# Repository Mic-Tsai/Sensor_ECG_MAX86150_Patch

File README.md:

# Sensor_ECG_PPG_MAX86150 | Patch

Arduino based sensor learning project. This project is further application from Health_Sensor_ecg_ppg_max86150 dev-board, plotting the ECG curve which used Processing on your computer.

 - Bias Cancellation | Store raw data in time, when new data coming that bias level will calculate as hysteresis filter.

 - Heart Rate Detect | Check windows will output the BPM results (ECG).

This board also support WiFi transmission via ESPNOW (ESP8266 Broadcast), and need power by battery. You need 2x esp8266 board.

1) Read receiver esp8266's mac address.
2) Fill it into the transmitter sketch. "ECG_ESP8266_MAX86150_V6"

** **A Known Issue** **

Sampling rate from MAX86150 set as 200sps, but ESP8266's multiplex with ESP-NOW and sensor hub reading task will low down the output sample rate to ~150sps. When you measuring your ECG in real-time plot may show the missing R-R interval. (R-peak missing!) Don't worry, it just the lower sample  caused.

```
Arduino tool kit, and require the following material:
- MCU: ESP8266 
- Sensor: MAX86150
```
##

For coding example, you need the following library:

* [protocentral_max86150_ecg_ppg](https://github.com/Protocentral/protocentral_max86150_ecg_ppg)

## 

Any question or need technical support:

* Contact me via mail (xbcke12345@gmail.com)

## 

## 

>### License Information
>>This product is open source! Both, our hardware and software are open source and licensed under the following:
>>#### Hardware
>>>All hardware is released under [Creative Commons Share-alike 4.0 International](http://creativecommons.org/licenses/by-sa/4.0/)
>>#### Software 
>>>All software is released under the MIT License [http://opensource.org/licenses/MIT](http://opensource.org/licenses/MIT)
>>#### Documentation
>>>The documentation on this page is released under [Creative Commons Share-alike 4.0 International](http://creativecommons.org/licenses/by-sa/4.0/)

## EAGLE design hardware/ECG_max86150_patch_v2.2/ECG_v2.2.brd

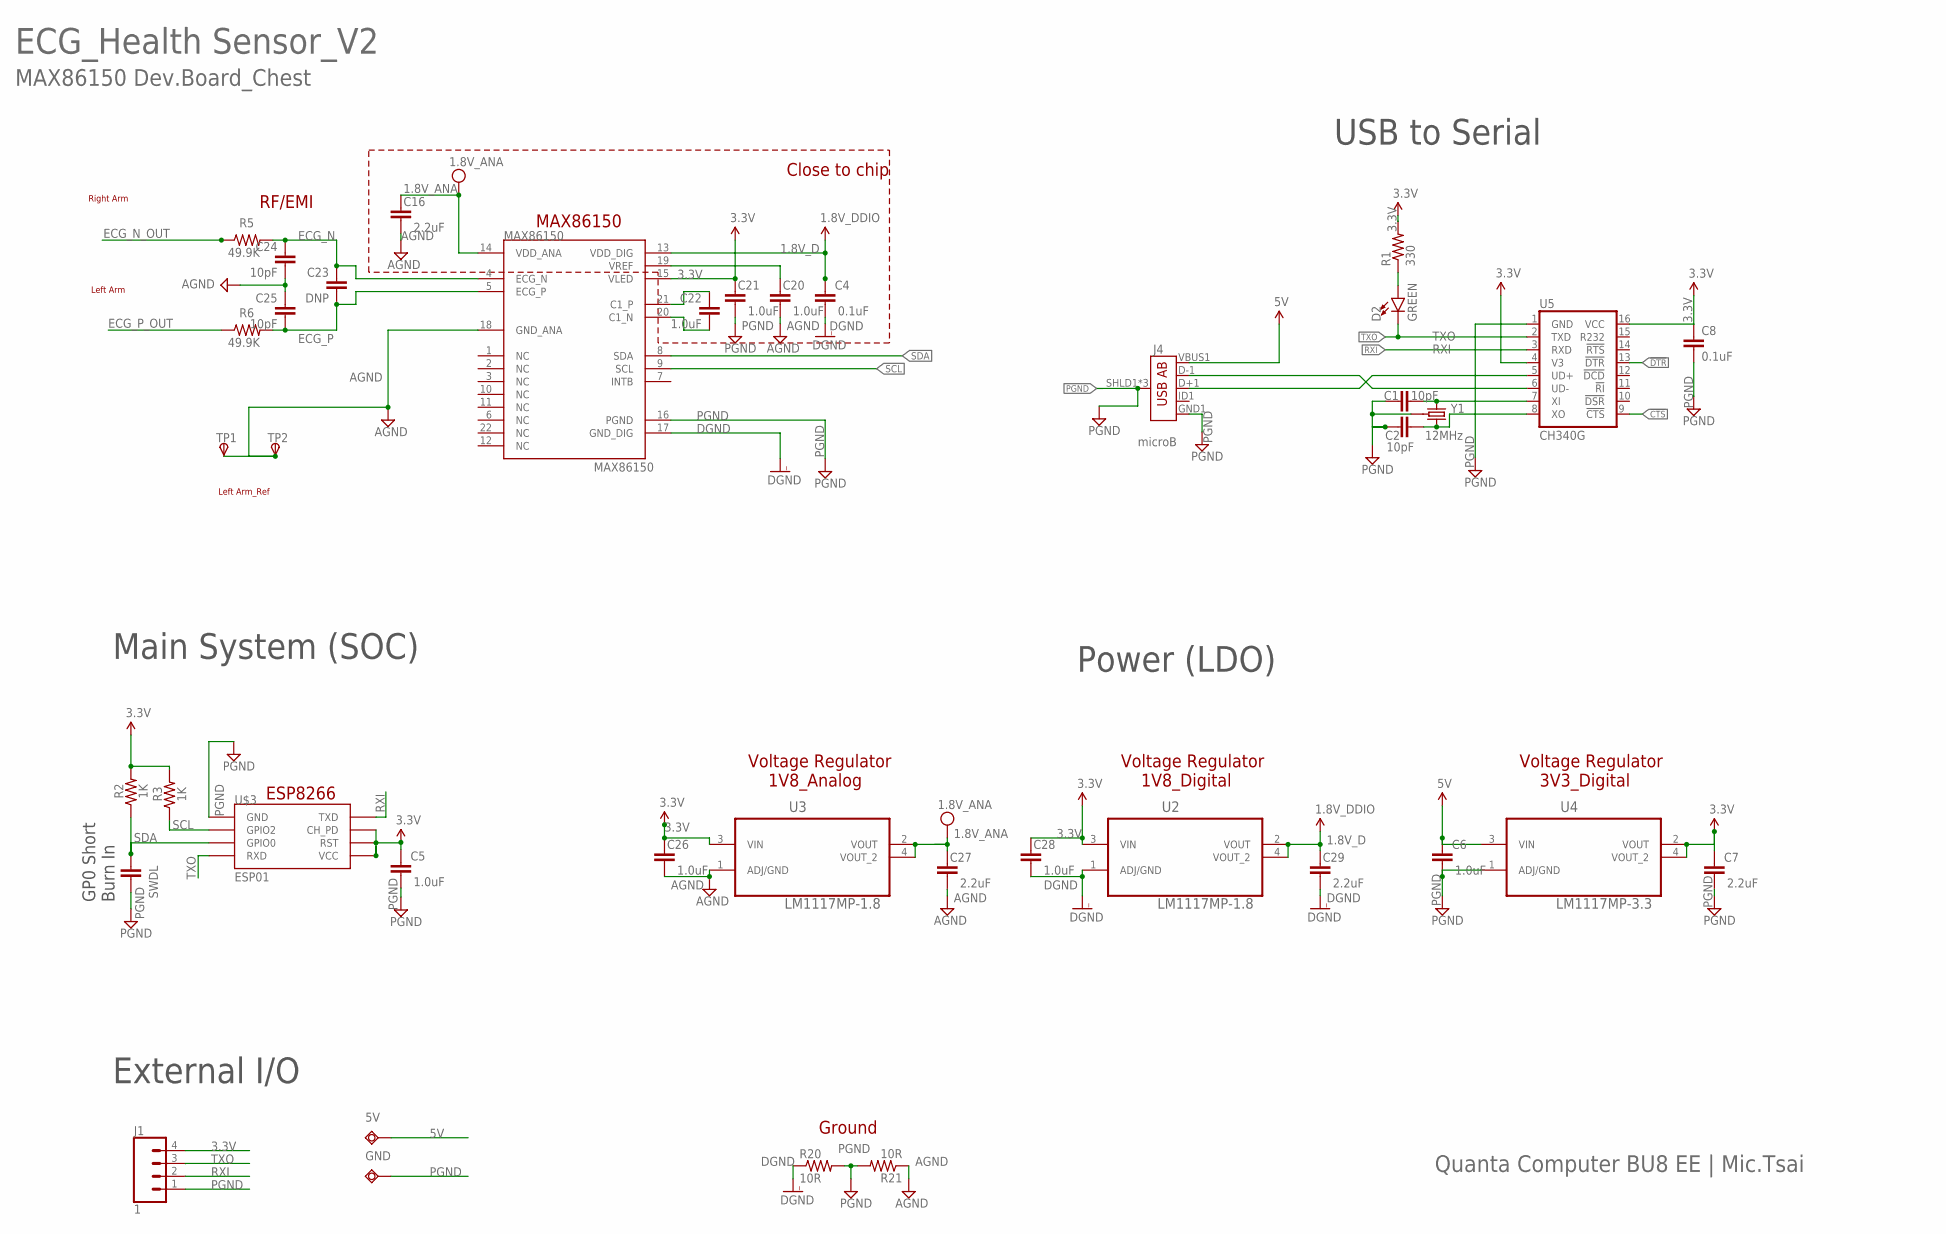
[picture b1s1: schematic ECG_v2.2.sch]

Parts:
5V: TPSQTP20R; TP20R
C1, C2: 10pF; 0603-CAP
C4: 0.1uF; 0805
C5, C6, C20, C21, C22, C26, C28: 1.0uF; 0805
C7, C16, C27, C29: 2.2uF; 0805
C8: 0.1uF; 0603-CAP
C23: DNP; 0402
C24, C25: 10pF; 0402
D2: GREEN; LED-0603
GND: TPSQTP20R; TP20R
J1: 1; 1X04
J4: microB; USB-AB-MICRO-SMD
MAX86150: MAX86150
R1: 330; 0603-RES
R2, R3: 1K; 0805
R5, R6: 49.9K; 0805
R20, R21: 10R; 0805
SWDL: 10pF; 0402
TP1, TP2: TPSB1,27; B1,27
U2, U3: LM1117MP-1.8; SOT230P696X180-4N
U4: LM1117MP-3.3; SOT230P696X180-4N
U5: CH340G; SO016
U$3: ESP01
Y1: 12MHz; CRYSTAL-SMD-3.2X2.5

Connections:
1.8V_ANA: C16.1, C27.1, MAX86150.14 (VDD_ANA), U3.2 (VOUT), U3.4 (VOUT_2)
1.8V_D: C4.1, C29.1, MAX86150.13 (VDD_DIG), U2.2 (VOUT), U2.4 (VOUT_2)
3.3V: C5.1, C7.1, C8.1, C21.1, C26.1, C28.1, J1.4, MAX86150.15 (VLED), R1.2, R2.2, R3.2, U2.3 (VIN), U3.3 (VIN), U4.2 (VOUT), U4.4 (VOUT_2), U5.4 (V3), U5.16 (VCC), U$3.CH_PD, U$3.RST, U$3.VCC
5V: 5V.TP, C6.1, J4.VBUS1 (VBUS), U4.3 (VIN)
!CTS: U5.9 (!CTS)
!DTR: U5.13 (!DTR)
AGND: C16.2, C20.2, C24.2, C25.1, C26.2, C27.2, MAX86150.18 (GND_ANA), R21.1, TP1.PP, TP2.PP, U3.1 (ADJ/GND)
DGND: C4.2, C28.2, C29.2, MAX86150.17 (GND_DIG), R20.1, U2.1 (ADJ/GND)
ECG_N: C23.1, C24.1, MAX86150.4 (ECG_N), R5.2
ECG_N_OUT: R5.1
ECG_P: C23.2, C25.2, MAX86150.5 (ECG_P), R6.2
ECG_P_OUT: R6.1
unnamed: D2.A, R1.1
unnamed: C22.1, MAX86150.21 (C1_P)
unnamed: C22.2, MAX86150.20 (C1_N)
unnamed: C20.1, MAX86150.19 (VREF)
unnamed: C2.2, U5.8 (XO), Y1.3 (2)
unnamed: C1.2, U5.7 (XI), Y1.1
unnamed: J4.D-1 (D-), U5.6 (UD-)
unnamed: J4.D+1 (D+), U5.5 (UD+)
PGND: C1.1, C2.1, C5.2, C6.2, C7.2, C8.2, C21.2, GND.TP, J1.1, J4.GND1 (GND), J4.SHLD1 (SHIELD), J4.SHLD2 (SHIELD), J4.SHLD3 (SHIELD), MAX86150.16 (PGND), R20.2, R21.2, SWDL.2, U4.1 (ADJ/GND), U5.1 (GND), U$3.GND, Y1.2 (GND), Y1.4 (GND)
RXI: J1.2, U5.3 (RXD), U$3.TX (TXD)
SCL: MAX86150.9 (SCL), R3.1, U$3.GPIO2
SDA: MAX86150.8 (SDA), R2.1, SWDL.1, U$3.GPIO0
TXO: D2.C, J1.3, U5.2 (TXD), U$3.RX (RXD)

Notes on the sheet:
Close to chip
ECG_Health Sensor_V2
MAX86150 Dev.Board_Chest
Quanta Computer BU8 EE | Mic.Tsai
Left Arm
RF/EMI
Ground
Right Arm
Left Arm_Ref
Voltage Regulator 1V8_Analog
Voltage Regulator 1V8_Digital
MAX86150
ESP8266
USB to Serial
GP0 Short Burn In
Voltage Regulator 3V3_Digital
Main System (SOC)
Power (LDO)
External I/O

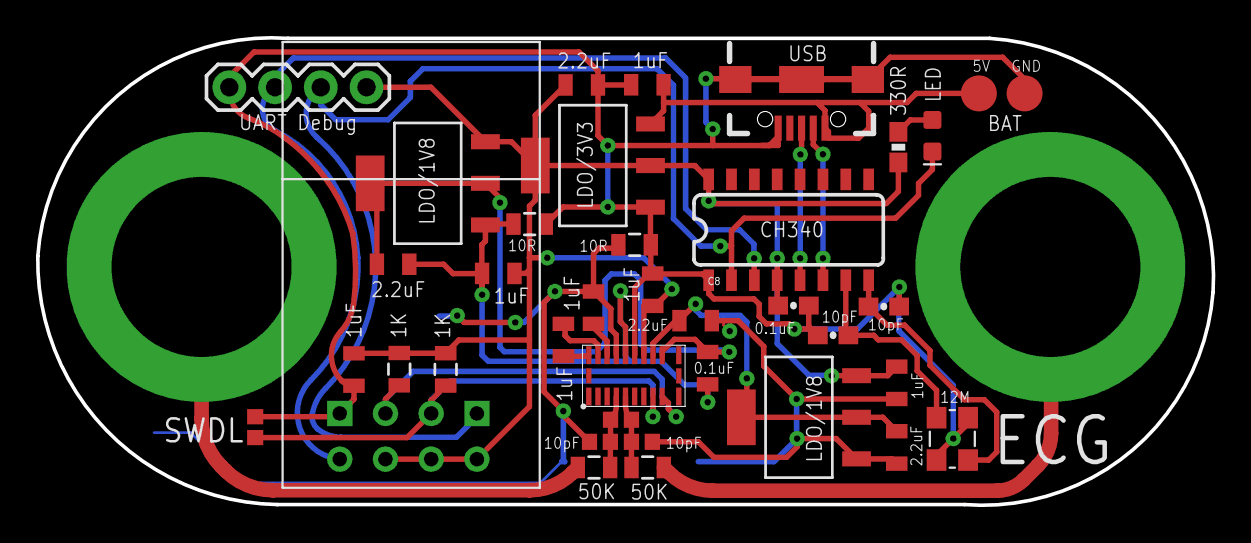
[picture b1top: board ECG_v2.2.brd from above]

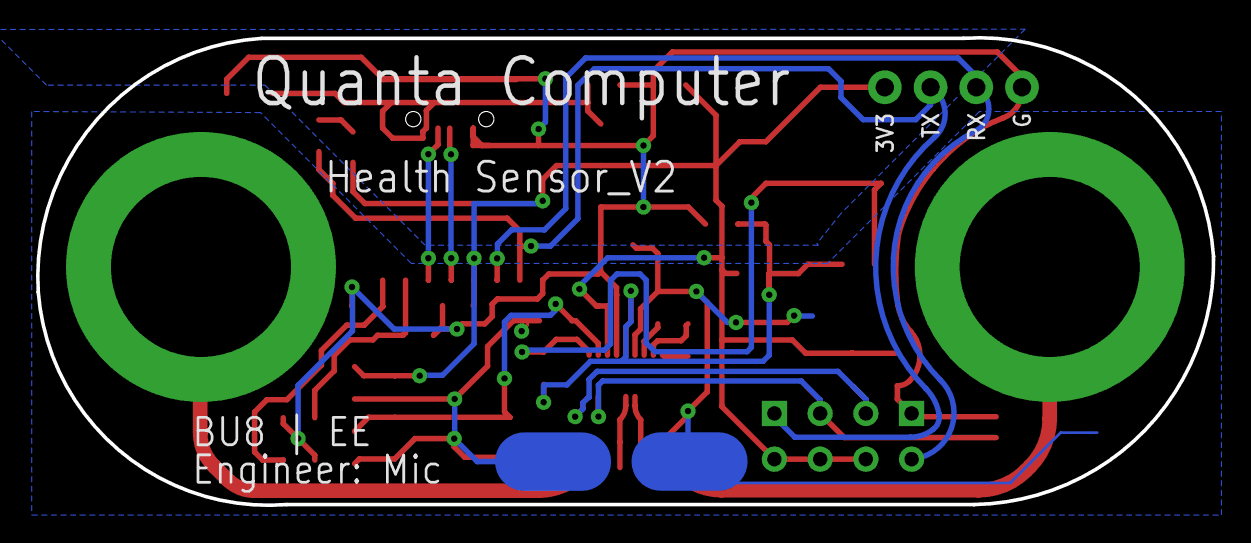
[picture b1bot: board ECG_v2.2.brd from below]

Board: 2 copper layers, 65.3 x 26.0 mm, 40 parts (2 on the bottom side), 21 nets.

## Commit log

2020-12-28 Upload files
    code, hardware, and introduction.

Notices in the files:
parts and their libraries:
SparkFun-Capacitors: Licensing: Creative Commons ShareAlike 4.0 International - https://creativecommons.org/licenses/by-sa/4.0
SparkFun-DigitalIC: Licensing: CC v3.0 Share-Alike You are welcome to use this library for commercial purposes.
